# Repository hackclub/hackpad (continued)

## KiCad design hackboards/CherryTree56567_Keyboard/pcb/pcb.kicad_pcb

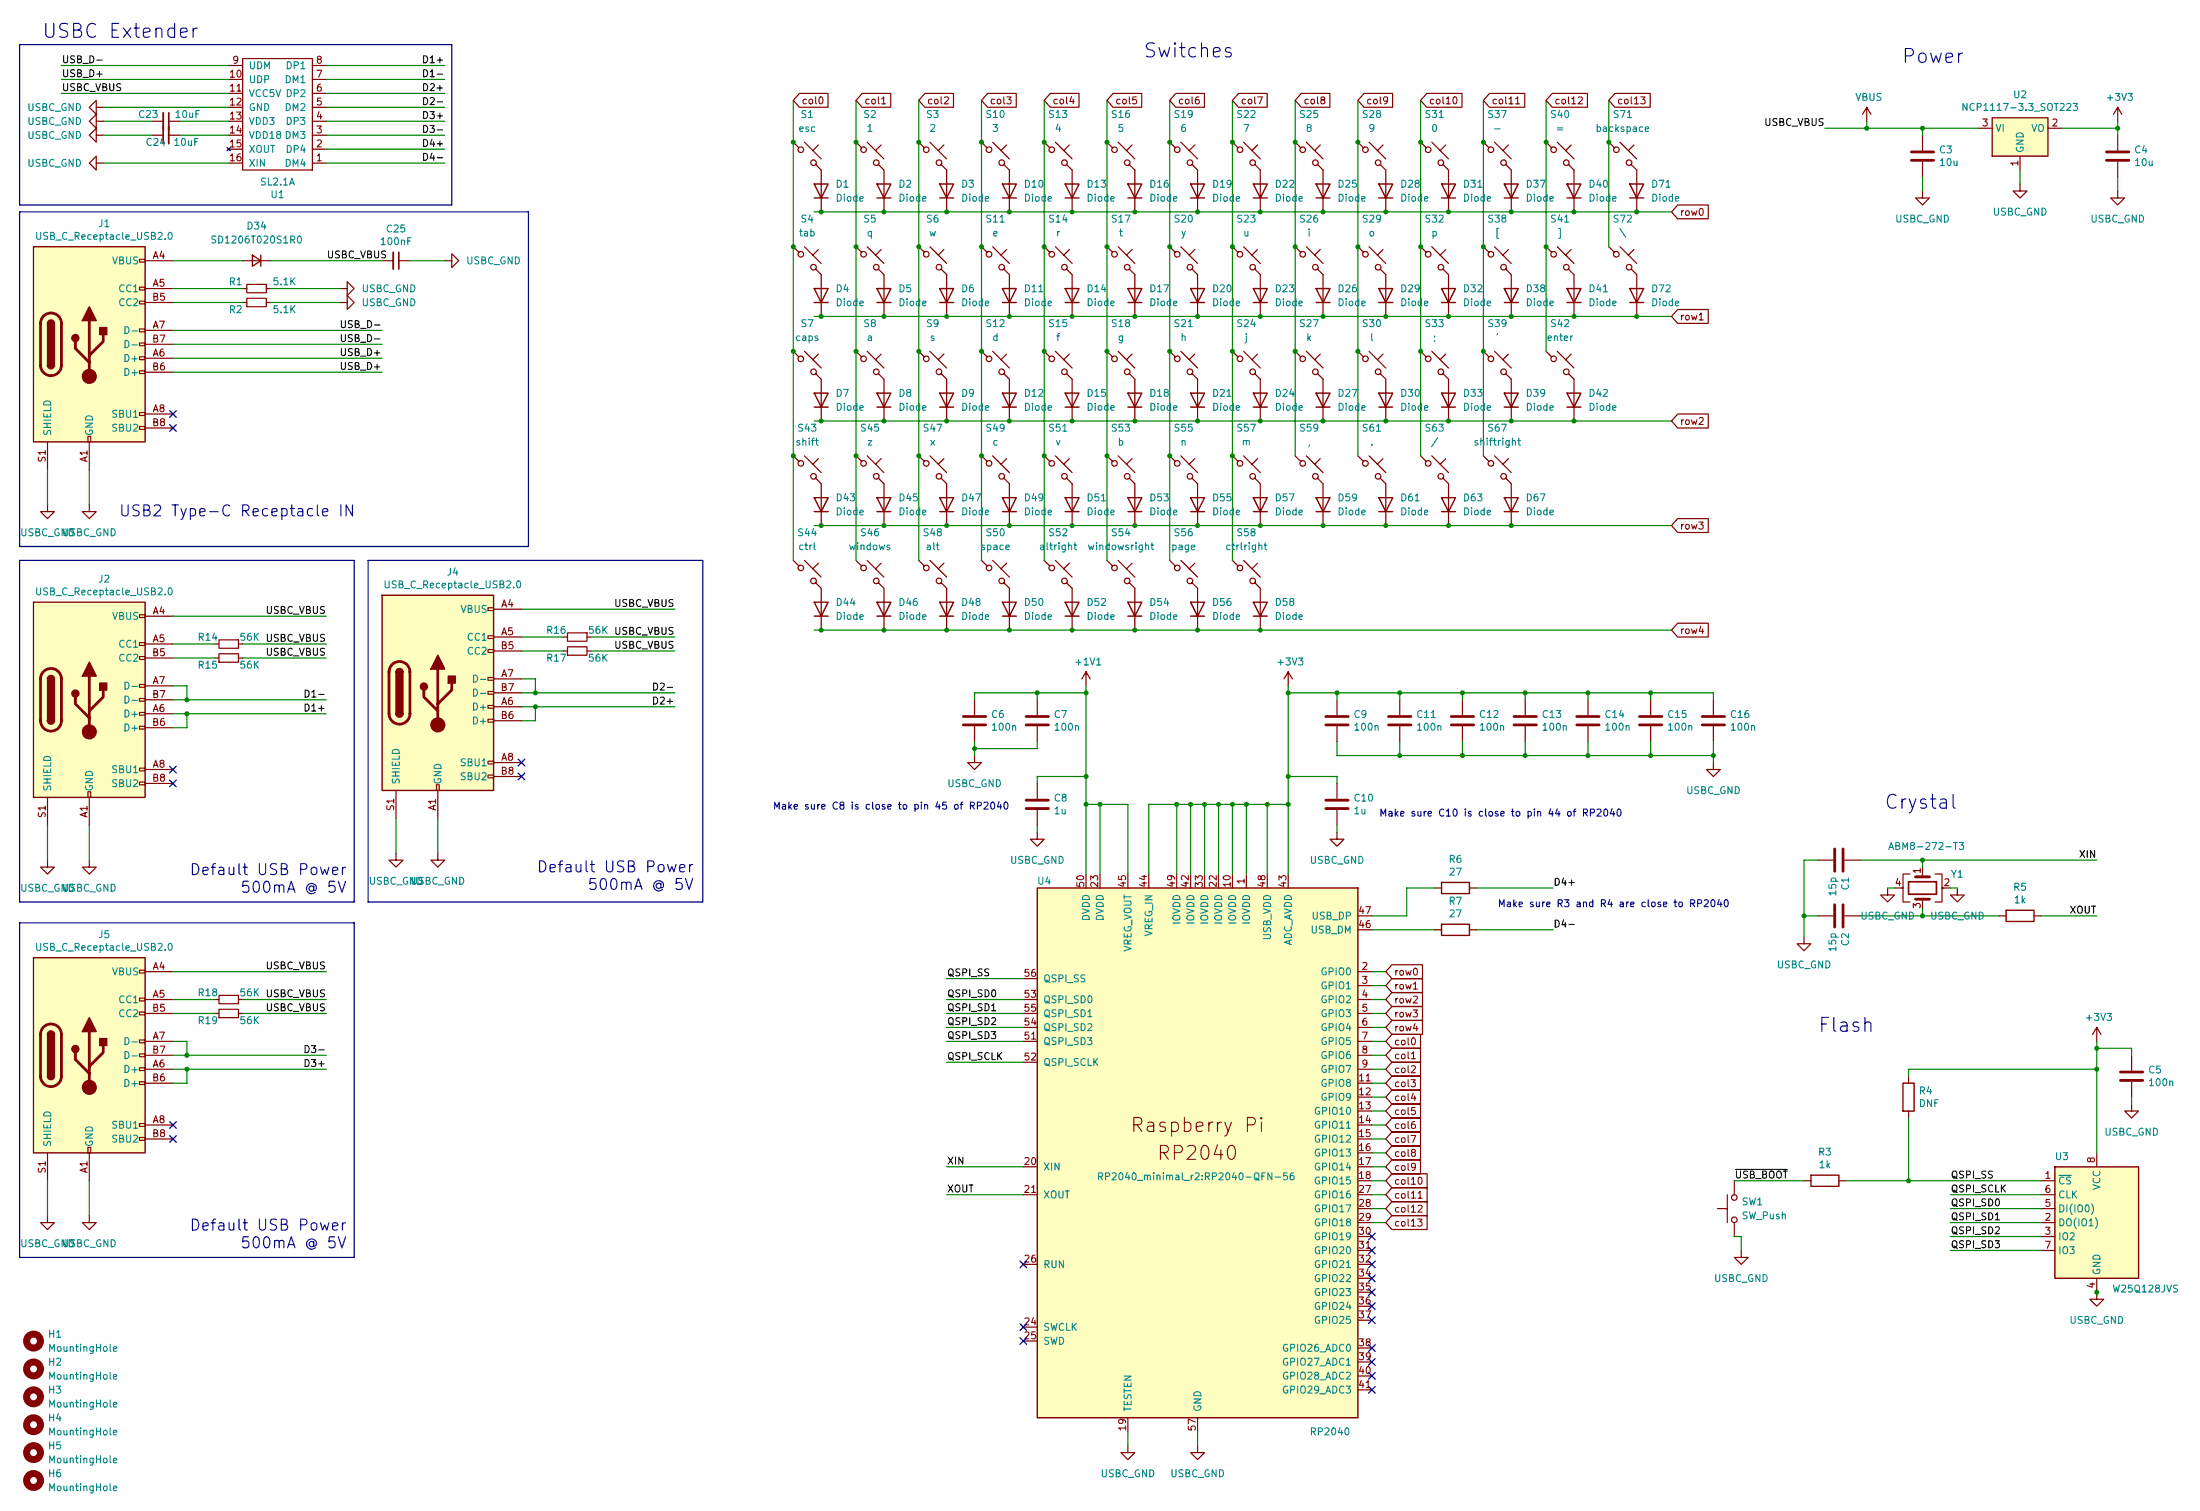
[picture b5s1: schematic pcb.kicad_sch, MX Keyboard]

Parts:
C1, C2: 15p; C_0402_1005Metric
C3, C4: 10u; C_0805_2012Metric
C5, C6, C7, C9, C11, C12, C13, C14, C15, C16: 100n; C_0402_1005Metric
C8, C10: 1u; C_0402_1005Metric
C23, C24: 10uF; C_0805_2012Metric_Pad1.18x1.45mm_HandSolder
C25: 100nF; C_0805_2012Metric_Pad1.18x1.45mm_HandSolder
D1, D2, D3, D4, D5, D6, D7, D8, D9, D10, D11, D12, D13, D14, D15, D16, D17, D18, D19, D20, D21, D22, D23, D24, D25, D26, D27, D28, D29, D30, D31, D32, D33, D37, D38, D39, D40, D41, D42, D43, D44, D45, D46, D47, D48, D49, D50, D51, D52, D53, D54, D55, D56, D57, D58, D59, D61, D63, D67, D71, D72: Diode; Diode_DO-35
D34: SD1206T020S1R0; D_1206_3216Metric_Pad1.42x1.75mm_HandSolder
H1, H2, H3, H4, H5, H6: MountingHole; MountingHole_2.1mm
J1, J2, J4, J5: USB_C_Receptacle_USB2.0; USB_C_Receptacle_HRO_TYPE-C-31-M-12
R1, R2: 5.1K; R_0805_2012Metric_Pad1.20x1.40mm_HandSolder
R3, R5: 1k; R_0402_1005Metric
R4: DNF; R_0402_1005Metric
R6, R7: 27; R_0402_1005Metric
R14, R15, R16, R17, R18, R19: 56K; R_0805_2012Metric_Pad1.20x1.40mm_HandSolder
S1: esc; SW_Hotswap_Kailh_MX_1.00u
S2: 1; SW_Hotswap_Kailh_MX_1.00u
S3: 2; SW_Hotswap_Kailh_MX_1.00u
S4: tab; SW_Hotswap_Kailh_MX_1.00u
S5: q; SW_Hotswap_Kailh_MX_1.00u
S6: w; SW_Hotswap_Kailh_MX_1.00u
S7: caps; SW_Hotswap_Kailh_MX_1.00u
S8: a; SW_Hotswap_Kailh_MX_1.00u
S9: s; SW_Hotswap_Kailh_MX_1.00u
S10: 3; SW_Hotswap_Kailh_MX_1.00u
S11: e; SW_Hotswap_Kailh_MX_1.00u
S12: d; SW_Hotswap_Kailh_MX_1.00u
S13: 4; SW_Hotswap_Kailh_MX_1.00u
S14: r; SW_Hotswap_Kailh_MX_1.00u
S15: f; SW_Hotswap_Kailh_MX_1.00u
S16: 5; SW_Hotswap_Kailh_MX_1.00u
S17: t; SW_Hotswap_Kailh_MX_1.00u
S18: g; SW_Hotswap_Kailh_MX_1.00u
S19: 6; SW_Hotswap_Kailh_MX_1.00u
S20: y; SW_Hotswap_Kailh_MX_1.00u
S21: h; SW_Hotswap_Kailh_MX_1.00u
S22: 7; SW_Hotswap_Kailh_MX_1.00u
S23: u; SW_Hotswap_Kailh_MX_1.00u
S24: j; SW_Hotswap_Kailh_MX_1.00u
S25: 8; SW_Hotswap_Kailh_MX_1.00u
S26: i; SW_Hotswap_Kailh_MX_1.00u
S27: k; SW_Hotswap_Kailh_MX_1.00u
S28: 9; SW_Hotswap_Kailh_MX_1.00u
S29: o; SW_Hotswap_Kailh_MX_1.00u
S30: l; SW_Hotswap_Kailh_MX_1.00u
S31: 0; SW_Hotswap_Kailh_MX_1.00u
S32: p; SW_Hotswap_Kailh_MX_1.00u
S33: ;; SW_Hotswap_Kailh_MX_1.00u
S37: -; SW_Hotswap_Kailh_MX_1.00u
S38: [; SW_Hotswap_Kailh_MX_1.00u
S39: '; SW_Hotswap_Kailh_MX_1.00u
S40: =; SW_Hotswap_Kailh_MX_1.00u
S41: ]; SW_Hotswap_Kailh_MX_1.00u
S42: enter; SW_Hotswap_Kailh_MX_2.25u
S43: shift; SW_Hotswap_Kailh_MX_2.00u
S44: ctrl; SW_Hotswap_Kailh_MX_1.25u
S45: z; SW_Hotswap_Kailh_MX_1.00u
S46: windows; SW_Hotswap_Kailh_MX_1.25u
S47: x; SW_Hotswap_Kailh_MX_1.00u
S48: alt; SW_Hotswap_Kailh_MX_1.25u
S49: c; SW_Hotswap_Kailh_MX_1.00u
S50: space; SW_Hotswap_Kailh_MX_6.25u
S51: v; SW_Hotswap_Kailh_MX_1.00u
S52: altright; SW_Hotswap_Kailh_MX_1.25u
S53: b; SW_Hotswap_Kailh_MX_1.00u
S54: windowsright; SW_Hotswap_Kailh_MX_1.25u
S55: n; SW_Hotswap_Kailh_MX_1.00u
S56: page; SW_Hotswap_Kailh_MX_1.00u
S57: m; SW_Hotswap_Kailh_MX_1.00u
S58: ctrlright; SW_Hotswap_Kailh_MX_1.25u
S59: ,; SW_Hotswap_Kailh_MX_1.00u
S61: .; SW_Hotswap_Kailh_MX_1.00u
S63: /; SW_Hotswap_Kailh_MX_1.00u
S67: shiftright; SW_Hotswap_Kailh_MX_2.75u
S71: backspace; SW_Hotswap_Kailh_MX_1.75u
S72: \; SW_Hotswap_Kailh_MX_1.25u
SW1: SW_Push; SW_Push_1P1T_NO_Vertical_Wuerth_434133025816
U1: SL2.1A; SOIC-16_4.55x10.3mm_P1.27mm
U2: NCP1117-3.3_SOT223; SOT-223-3_TabPin2
U3: W25Q128JVS; SOIC-8_5.23x5.23mm_P1.27mm
U4: RP2040; RP2040-QFN-56
Y1: ABM8-272-T3; Crystal_SMD_3225-4Pin_3.2x2.5mm

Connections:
+1V1: C6.1, C7.1, C8.1, U4.23 (DVDD), U4.45 (VREG_VOUT), U4.50 (DVDD)
+3V3: C4.1, C5.1, C9.1, C10.1, C11.1, C12.1, C13.1, C14.1, C15.1, C16.1, R4.1, U2.2 (VO), U3.8 (VCC), U4.1 (IOVDD), U4.10 (IOVDD), U4.22 (IOVDD), U4.33 (IOVDD), U4.42 (IOVDD), U4.43 (ADC_AVDD), U4.44 (VREG_IN), U4.48 (USB_VDD), U4.49 (IOVDD)
/D1+: J2.A6 (D+), J2.B6 (D+), U1.8 (DP1)
/D1-: J2.A7 (D-), J2.B7 (D-), U1.7 (DM1)
/D2+: J4.A6 (D+), J4.B6 (D+), U1.6 (DP2)
/D2-: J4.A7 (D-), J4.B7 (D-), U1.5 (DM2)
/D3+: J5.A6 (D+), J5.B6 (D+), U1.4 (DP3)
/D3-: J5.A7 (D-), J5.B7 (D-), U1.3 (DM3)
/D4+: R6.1, U1.2 (DP4)
/D4-: R7.1, U1.1 (DM4)
/QSPI_SCLK: U3.6 (CLK), U4.52 (QSPI_SCLK)
/QSPI_SD0: U3.5 (DI(IO0)), U4.53 (QSPI_SD0)
/QSPI_SD1: U3.2 (DO(IO1)), U4.55 (QSPI_SD1)
/QSPI_SD2: U3.3 (IO2), U4.54 (QSPI_SD2)
/QSPI_SD3: U3.7 (IO3), U4.51 (QSPI_SD3)
/QSPI_SS: R3.1, R4.2, U3.1 (~CS), U4.56 (QSPI_SS)
/USB_D+: J1.A6 (D+), J1.B6 (D+), U1.10 (UDP)
/USB_D-: J1.A7 (D-), J1.B7 (D-), U1.9 (UDM)
/XIN: C1.1, U4.20 (XIN), Y1.1
/XOUT: R5.1, U4.21 (XOUT)
/~USB_BOOT: R3.2, SW1.2
unnamed: C2.1, R5.2, Y1.3
unnamed: D1.2 (A), S1.2
unnamed: D2.2 (A), S2.2
unnamed: D3.2 (A), S3.2
unnamed: D4.2 (A), S4.2
unnamed: D5.2 (A), S5.2
unnamed: D6.2 (A), S6.2
unnamed: D7.2 (A), S7.2
unnamed: D8.2 (A), S8.2
unnamed: D9.2 (A), S9.2
unnamed: D10.2 (A), S10.2
unnamed: D11.2 (A), S11.2
unnamed: D12.2 (A), S12.2
unnamed: D13.2 (A), S13.2
unnamed: D14.2 (A), S14.2
unnamed: D15.2 (A), S15.2
unnamed: D16.2 (A), S16.2
unnamed: D17.2 (A), S17.2
unnamed: D18.2 (A), S18.2
unnamed: D19.2 (A), S19.2
unnamed: D20.2 (A), S20.2
unnamed: D21.2 (A), S21.2
unnamed: D22.2 (A), S22.2
unnamed: D23.2 (A), S23.2
unnamed: D24.2 (A), S24.2
unnamed: D25.2 (A), S25.2
unnamed: D26.2 (A), S26.2
unnamed: D27.2 (A), S27.2
unnamed: D28.2 (A), S28.2
unnamed: D29.2 (A), S29.2
unnamed: D30.2 (A), S30.2
unnamed: D31.2 (A), S31.2
unnamed: D32.2 (A), S32.2
unnamed: D33.2 (A), S33.2
unnamed: D34.2 (A), J1.A4 (VBUS), J1.A9 (VBUS), J1.B4 (VBUS), J1.B9 (VBUS)
unnamed: D37.2 (A), S37.2
unnamed: D38.2 (A), S38.2
unnamed: D39.2 (A), S39.2
unnamed: D40.2 (A), S40.2
unnamed: D41.2 (A), S41.2
unnamed: D42.2 (A), S42.2
unnamed: D43.2 (A), S43.2
unnamed: D44.2 (A), S44.2
unnamed: D45.2 (A), S45.2
unnamed: D46.2 (A), S46.2
unnamed: D47.2 (A), S47.2
unnamed: D48.2 (A), S48.2
unnamed: D49.2 (A), S49.2
unnamed: D50.2 (A), S50.2
unnamed: D51.2 (A), S51.2
unnamed: D52.2 (A), S52.2
unnamed: D53.2 (A), S53.2
unnamed: D54.2 (A), S54.2
unnamed: D55.2 (A), S55.2
unnamed: D56.2 (A), S56.2
unnamed: D57.2 (A), S57.2
unnamed: D58.2 (A), S58.2
unnamed: D59.2 (A), S59.2
unnamed: D61.2 (A), S61.2
unnamed: D63.2 (A), S63.2
unnamed: D67.2 (A), S67.2
unnamed: D71.2 (A), S71.2
unnamed: D72.2 (A), S72.2
unnamed: J1.A5 (CC1), R1.2
unnamed: J1.B5 (CC2), R2.1
unnamed: J2.A5 (CC1), R14.2
unnamed: J2.B5 (CC2), R15.1
unnamed: J4.A5 (CC1), R16.2
unnamed: J4.B5 (CC2), R17.1
unnamed: J5.A5 (CC1), R18.2
unnamed: J5.B5 (CC2), R19.1
unnamed: C23.1, U1.13 (VDD3)
unnamed: C24.2, U1.14 (VDD18)
unnamed: R7.2, U4.46 (USB_DM)
unnamed: R6.2, U4.47 (USB_DP)
USBC_GND: C1.2, C2.2, C3.2, C4.2, C5.2, C6.2, C7.2, C8.2, C9.2, C10.2, C11.2, C12.2, C13.2, C14.2, C15.2, C16.2, C23.2, C24.1, C25.1, J1.A1 (GND), J1.A12 (GND), J1.B1 (GND), J1.B12 (GND), J1.S1 (SHIELD), J2.A1 (GND), J2.A12 (GND), J2.B1 (GND), J2.B12 (GND), J2.S1 (SHIELD), J4.A1 (GND), J4.A12 (GND), J4.B1 (GND), J4.B12 (GND), J4.S1 (SHIELD), J5.A1 (GND), J5.A12 (GND), J5.B1 (GND), J5.B12 (GND), J5.S1 (SHIELD), R1.1, R2.2, SW1.1, U1.12 (GND), U1.16 (XIN), U2.1 (GND), U3.4 (GND), U4.19 (TESTEN), U4.57 (GND), Y1.2, Y1.4
VBUS: C3.1, C25.2, D34.1 (K), J2.A4 (VBUS), J2.A9 (VBUS), J2.B4 (VBUS), J2.B9 (VBUS), J4.A4 (VBUS), J4.A9 (VBUS), J4.B4 (VBUS), J4.B9 (VBUS), J5.A4 (VBUS), J5.A9 (VBUS), J5.B4 (VBUS), J5.B9 (VBUS), R14.1, R15.2, R16.1, R17.2, R18.1, R19.2, U1.11 (VCC5V), U2.3 (VI)
col0: S1.1, S4.1, S7.1, S43.1, S44.1, U4.7 (GPIO5)
col1: S2.1, S5.1, S8.1, S45.1, S46.1, U4.8 (GPIO6)
col2: S3.1, S6.1, S9.1, S47.1, S48.1, U4.9 (GPIO7)
col3: S10.1, S11.1, S12.1, S49.1, S50.1, U4.11 (GPIO8)
col4: S13.1, S14.1, S15.1, S51.1, S52.1, U4.12 (GPIO9)
col5: S16.1, S17.1, S18.1, S53.1, S54.1, U4.13 (GPIO10)
col6: S19.1, S20.1, S21.1, S55.1, S56.1, U4.14 (GPIO11)
col7: S22.1, S23.1, S24.1, S57.1, S58.1, U4.15 (GPIO12)
col8: S25.1, S26.1, S27.1, S59.1, U4.16 (GPIO13)
col9: S28.1, S29.1, S30.1, S61.1, U4.17 (GPIO14)
col10: S31.1, S32.1, S33.1, S63.1, U4.18 (GPIO15)
col11: S37.1, S38.1, S39.1, S67.1, U4.27 (GPIO16)
col12: S40.1, S41.1, S42.1, U4.28 (GPIO17)
col13: S71.1, S72.1, U4.29 (GPIO18)
row0: D1.1 (K), D2.1 (K), D3.1 (K), D10.1 (K), D13.1 (K), D16.1 (K), D19.1 (K), D22.1 (K), D25.1 (K), D28.1 (K), D31.1 (K), D37.1 (K), D40.1 (K), D71.1 (K), U4.2 (GPIO0)
row1: D4.1 (K), D5.1 (K), D6.1 (K), D11.1 (K), D14.1 (K), D17.1 (K), D20.1 (K), D23.1 (K), D26.1 (K), D29.1 (K), D32.1 (K), D38.1 (K), D41.1 (K), D72.1 (K), U4.3 (GPIO1)
row2: D7.1 (K), D8.1 (K), D9.1 (K), D12.1 (K), D15.1 (K), D18.1 (K), D21.1 (K), D24.1 (K), D27.1 (K), D30.1 (K), D33.1 (K), D39.1 (K), D42.1 (K), U4.4 (GPIO2)
row3: D43.1 (K), D45.1 (K), D47.1 (K), D49.1 (K), D51.1 (K), D53.1 (K), D55.1 (K), D57.1 (K), D59.1 (K), D61.1 (K), D63.1 (K), D67.1 (K), U4.5 (GPIO3)
row4: D44.1 (K), D46.1 (K), D48.1 (K), D50.1 (K), D52.1 (K), D54.1 (K), D56.1 (K), D58.1 (K), U4.6 (GPIO4)

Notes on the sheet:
Make sure C8 is close to pin 45 of RP2040
Default USB Power 500mA @ 5V
Make sure C10 is close to pin 44 of RP2040
USBC Extender
Switches
Make sure R3 and R4 are close to RP2040
Flash
Power
USB2 Type-C Receptacle IN
Crystal

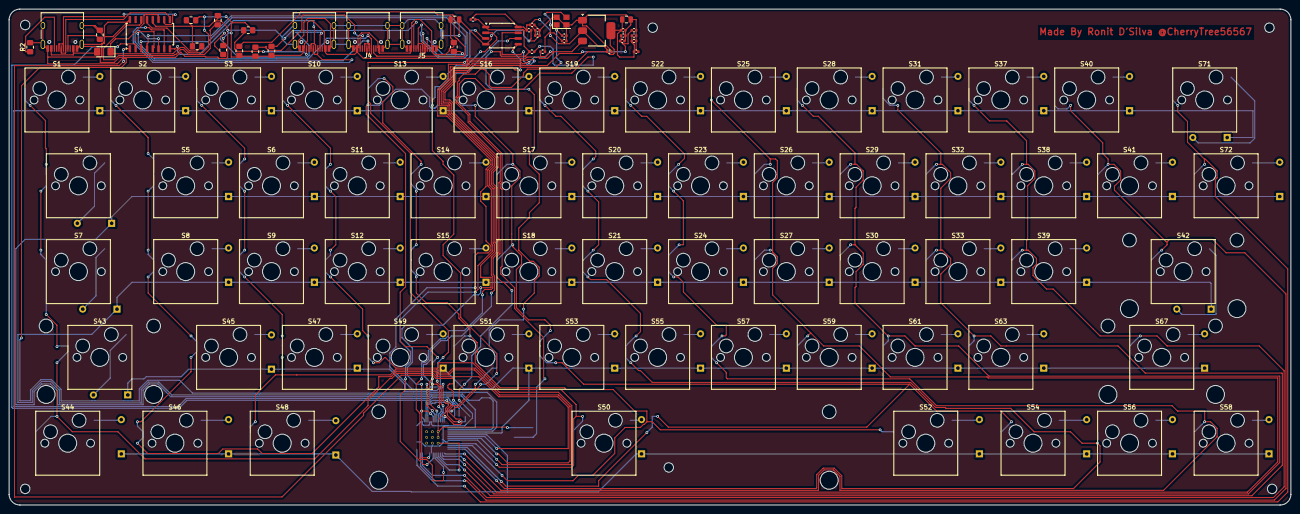
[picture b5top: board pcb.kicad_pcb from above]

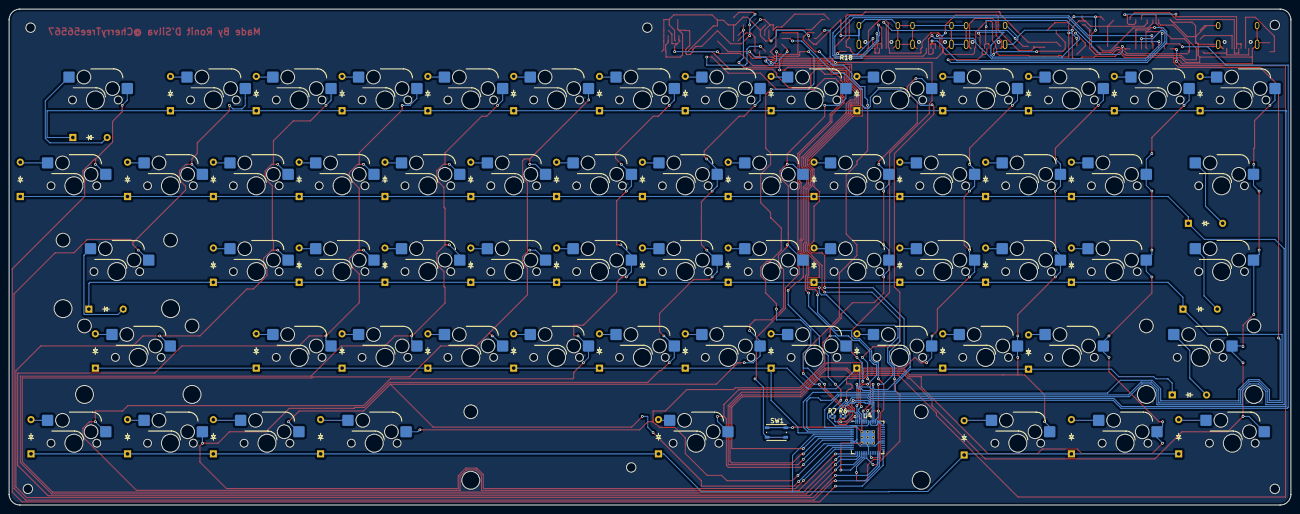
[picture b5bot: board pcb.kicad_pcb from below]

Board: 2 copper layers, 284.6 x 110.1 mm, 171 parts (65 on the bottom side), 117 nets.

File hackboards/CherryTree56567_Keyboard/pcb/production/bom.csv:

Designator,Footprint,Quantity,Value,LCSC Part #
"C23, C24",0805,2,10uF,
C25,0805,1,100nF,
"D1, D10, D11, D12, D13, D14, D15, D16, D17, D18, D19, D2, D20, D21, D22, D23, D24, D25, D26, D27, D28, D29, D3, D30, D31, D32, D33, D37, D38, D39, D4, D40, D41, D42, D43, D44, D45, D46, D47, D48, D49, D5, D50, D51, D52, D53, D54, D55, D56, D57, D58, D59, D6, D61, D63, D67, D7, D71, D72, D8, D9",Diode_DO-35,61,Diode,
D34,1206,1,SD1206T020S1R0,
"J1, J2, J4, J5",USB_C_Receptacle_HRO_TYPE-C-31-M-12,4,USB_C_Receptacle_USB2.0,
J6,PGA2040_PTH_NO_SLOT,1,PGA2040,
"R1, R2",0805,2,5.1K,
"R14, R15, R16, R17, R18, R19",0805,6,56K,
S1,MX_PCB_1.00u,1,esc,
S10,MX_PCB_1.00u,1,3,
S11,MX_PCB_1.00u,1,e,
S12,MX_PCB_1.00u,1,d,
S13,MX_PCB_1.00u,1,4,
S14,MX_PCB_1.00u,1,r,
S15,MX_PCB_1.00u,1,f,
S16,MX_PCB_1.00u,1,5,
S17,MX_PCB_1.00u,1,t,
S18,MX_PCB_1.00u,1,g,
S19,MX_PCB_1.00u,1,6,
S2,MX_PCB_1.00u,1,1,
S20,MX_PCB_1.00u,1,y,
S21,MX_PCB_1.00u,1,h,
S22,MX_PCB_1.00u,1,7,
S23,MX_PCB_1.00u,1,u,
S24,MX_PCB_1.00u,1,j,
S25,MX_PCB_1.00u,1,8,
S26,MX_PCB_1.00u,1,i,
S27,MX_PCB_1.00u,1,k,
S28,MX_PCB_1.00u,1,9,
S29,MX_PCB_1.00u,1,o,
S3,MX_PCB_1.00u,1,2,
S30,MX_PCB_1.00u,1,l,
S31,MX_PCB_1.00u,1,0,
S32,MX_PCB_1.00u,1,p,
S33,MX_PCB_1.00u,1,;,
S37,MX_PCB_1.00u,1,-,
S38,MX_PCB_1.00u,1,[,
S39,MX_PCB_1.00u,1,',
S4,MX_PCB_1.00u,1,tab,
S40,MX_PCB_1.00u,1,=,
S41,MX_PCB_1.00u,1,],
S42,MX_PCB_1.00u,1,enter,
S43,MX_PCB_1.00u,1,shift,
S44,MX_PCB_1.00u,1,ctrl,
S45,MX_PCB_1.00u,1,z,
S46,MX_PCB_1.00u,1,windows,
S47,MX_PCB_1.00u,1,x,
S48,MX_PCB_1.00u,1,alt,
S49,MX_PCB_1.00u,1,c,
S5,MX_PCB_1.00u,1,q,
S50,MX_PCB_1.00u,1,space,
S51,MX_PCB_1.00u,1,v,
S52,MX_PCB_1.00u,1,altright,
S53,MX_PCB_1.00u,1,b,
S54,MX_PCB_1.00u,1,windowsright,
S55,MX_PCB_1.00u,1,n,
S56,MX_PCB_1.00u,1,page,
S57,MX_PCB_1.00u,1,m,
S58,MX_PCB_1.00u,1,ctrlright,
S59,MX_PCB_1.00u,1,",",
S6,MX_PCB_1.00u,1,w,
S61,MX_PCB_1.00u,1,.,
S63,MX_PCB_1.00u,1,/,
S67,MX_PCB_1.00u,1,shiftright,
S7,MX_PCB_1.00u,1,caps,
S71,MX_PCB_1.00u,1,backspace,
S72,MX_PCB_1.00u,1,\,
S8,MX_PCB_1.00u,1,a,
S9,MX_PCB_1.00u,1,s,
SW3,SW_Push_1P1T_NO_Vertical_Wuerth_434133025816,1,RESET,
SW4,SW_Push_1P1T_NO_Vertical_Wuerth_434133025816,1,BOOTSEL,
U1,SOIC-16_4.55x10.3mm_P1.27mm,1,SL2.1A,
